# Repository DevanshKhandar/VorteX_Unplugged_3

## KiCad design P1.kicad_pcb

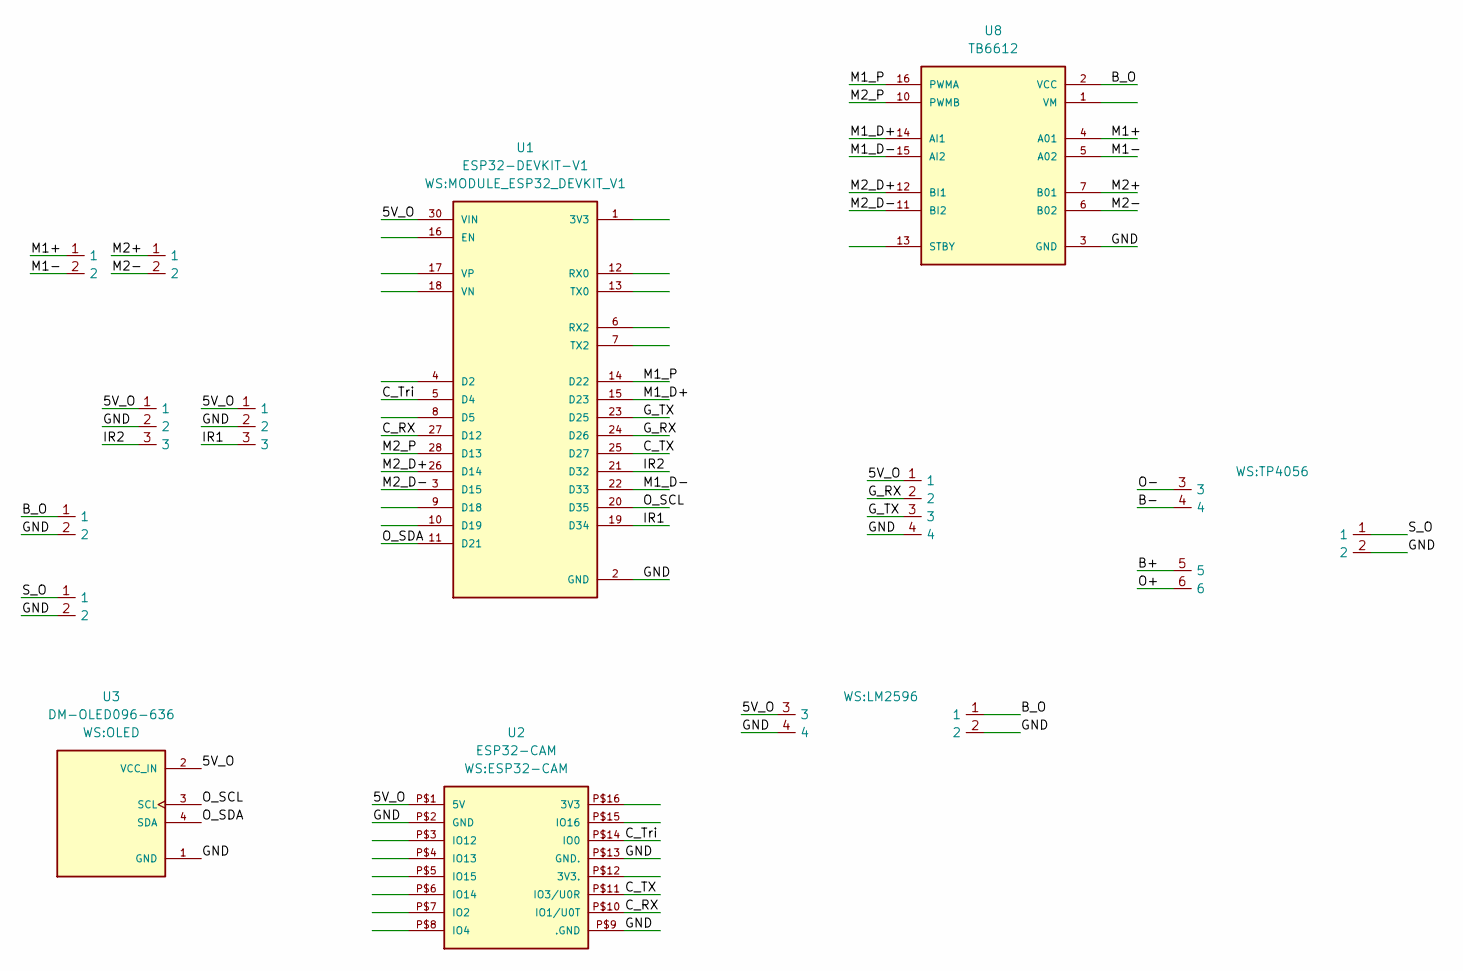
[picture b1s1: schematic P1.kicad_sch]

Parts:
U1: ESP32-DEVKIT-V1; MODULE_ESP32_DEVKIT_V1; PARTREV N/A
U2: ESP32-CAM
U3: DM-OLED096-636; OLED; PARTREV 2018-09-10
U4: 3P Header; LM2596
U5, U6: 3P Header; 2pin Header_SP
U7: 3P Header; Neo 6-M
U8: TB6612; PARTREV 11-13-17
U10, U11: 3P Header; XT30_Motora
U13, U15: 3P Header; 3pin Header_IR
U14: 3P Header; TP4056

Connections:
/5V_O: U1.30 (VIN), U2.P$1 (5V), U3.2 (VCC_IN), U4.3, U7.1, U13.1, U15.1
/B+: U14.5
/B-: U14.4
/B_O: U4.1, U5.1, U8.2 (VCC)
/C_RX: U1.27 (D12), U2.P$10 (IO1/U0T)
/C_TX: U1.25 (D27), U2.P$11 (IO3/U0R)
/C_Tri: U1.5 (D4), U2.P$14 (IO0)
/G_RX: U1.24 (D26), U7.2
/G_TX: U1.23 (D25), U7.3
/IR1: U1.19 (D34), U15.3
/IR2: U1.21 (D32), U13.3
/M1+: U8.4 (A01), U11.1
/M1-: U8.5 (A02), U11.2
/M1_D+: U1.15 (D23), U8.14 (AI1)
/M1_D-: U1.22 (D33), U8.15 (AI2)
/M1_P: U1.14 (D22), U8.16 (PWMA)
/M2+: U8.7 (B01), U10.1
/M2-: U8.6 (B02), U10.2
/M2_D+: U1.26 (D14), U8.12 (BI1)
/M2_D-: U1.3 (D15), U8.11 (BI2)
/M2_P: U1.28 (D13), U8.10 (PWMB)
/O+: U14.6
/O-: U14.3
/O_SCL: U1.20 (D35), U3.3 (SCL)
/O_SDA: U1.11 (D21), U3.4 (SDA)
/S_O: U6.1, U14.1
GND: U1.2 (GND), U1.29 (GND), U2.P$2 (GND), U2.P$9 (.GND), U2.P$13 (GND.), U3.1 (GND), U4.2, U4.4, U5.2, U6.2, U7.4, U8.3 (GND), U8.8 (GND), U8.9 (GND), U13.2, U14.2, U15.2

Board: 2 copper layers, 13 parts (1 on the bottom side), 23 nets, no tracks yet.
